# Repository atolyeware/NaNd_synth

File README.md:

NaNd_synth
==========

NaNd synth from Nicolas Collins' Book

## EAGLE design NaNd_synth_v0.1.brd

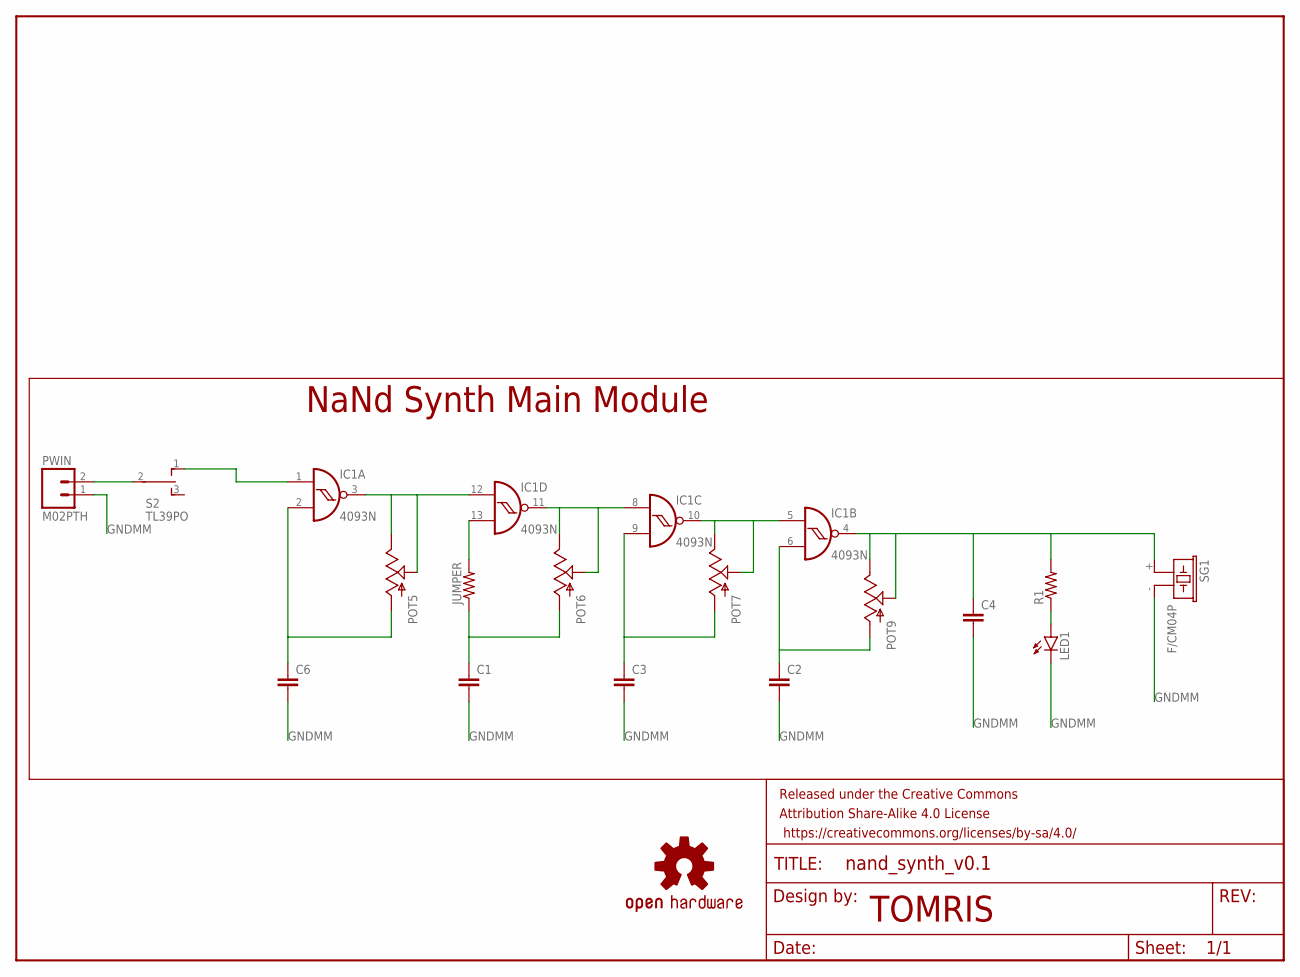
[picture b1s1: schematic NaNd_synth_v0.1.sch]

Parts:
C1, C2, C3, C4, C6: CAPPTH1; CAP-PTH-5MM
FRAME1: FRAME-LETTER; CREATIVE_COMMONS
IC1: 4093N; DIL14
JUMPER: RESISTORAXIAL-0.3; AXIAL-0.3
LED1: LED-3MM-NO_SILK; LED3MM-NS
LOGO1: OSHW-LOGOM; OSHW-LOGO-M
POT5, POT6, POT7, POT9: POTMAM; POT_MAMMOTH
PWIN: M02PTH; 1X02
R1: RESISTORAXIAL-0.3; AXIAL-0.3
S2: TL39PO; TL3XPO
SG1: F/CM04P

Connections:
GNDMM: C1.2, C2.2, C3.2, C4.2, C6.2, LED1.K (C), PWIN.1, SG1.- (2)
unnamed: C3.1, IC1.9 (I1), POT7.P$2 (A)
unnamed: C2.1, IC1.6 (I1), POT9.P$2 (A)
unnamed: LED1.A, R1.P$1 (1)
unnamed: PWIN.2, S2.2
unnamed: IC1.1 (I0), S2.1 (O)
unnamed: IC1.13 (I1), JUMPER.P$2 (2)
POTL2I: C6.1, IC1.2 (I1), POT5.P$2 (A)
POTL3I: IC1.3 (O), IC1.12 (I0), POT5.P$1 (S), POT5.P$3 (E)
POTL4I: IC1.8 (I0), IC1.11 (O), POT6.P$1 (S), POT6.P$3 (E)
POTL6I: C1.1, JUMPER.P$1 (1), POT6.P$2 (A)
POTL10I: IC1.5 (I0), IC1.10 (O), POT7.P$1 (S), POT7.P$3 (E)
POTL11I: C4.1, IC1.4 (O), POT9.P$1 (S), POT9.P$3 (E), R1.P$2 (2), SG1.+ (1)
VDD: IC1.14 (VDD)
VSS: IC1.7 (VSS)

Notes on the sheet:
NaNd Synth Main Module
TOMRIS

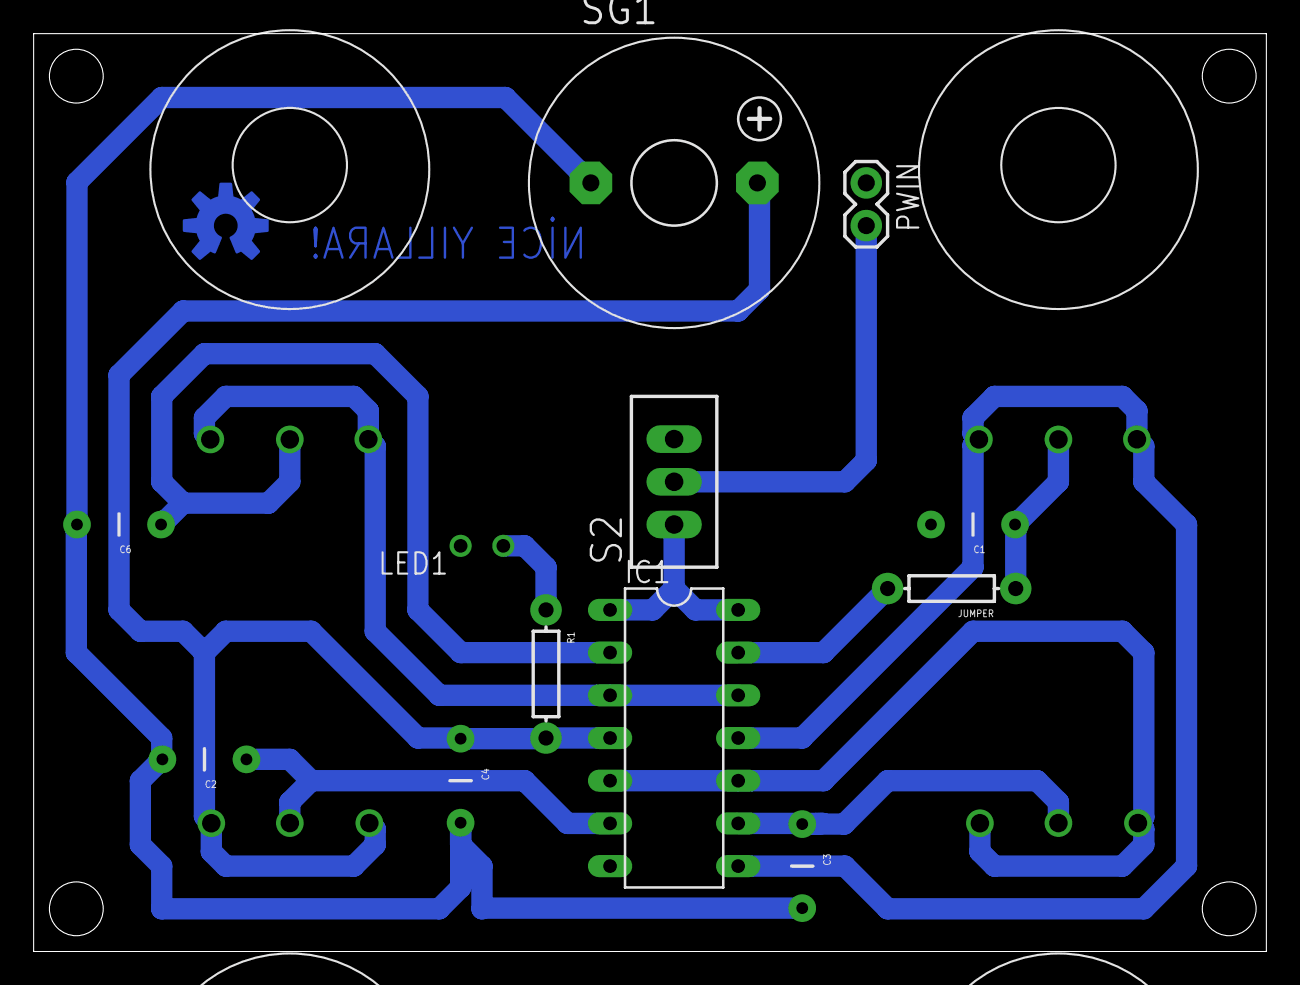
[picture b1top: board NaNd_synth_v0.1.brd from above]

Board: 2 copper layers, 73.3 x 54.6 mm, 18 parts (0 on the bottom side), 13 nets.

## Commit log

2016-08-26 add initial design files
    add initial files

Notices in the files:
parts and their libraries:
SparkFun-Aesthetics: Licensing: Creative Commons ShareAlike 4.0 International - https://creativecommons.org/licenses/by-sa/4.0
SparkFun-Aesthetics: Released under the Creative Commons Attribution Share-Alike 4.0 License
SparkFun-Aesthetics: https://creativecommons.org/licenses/by-sa/4.0
